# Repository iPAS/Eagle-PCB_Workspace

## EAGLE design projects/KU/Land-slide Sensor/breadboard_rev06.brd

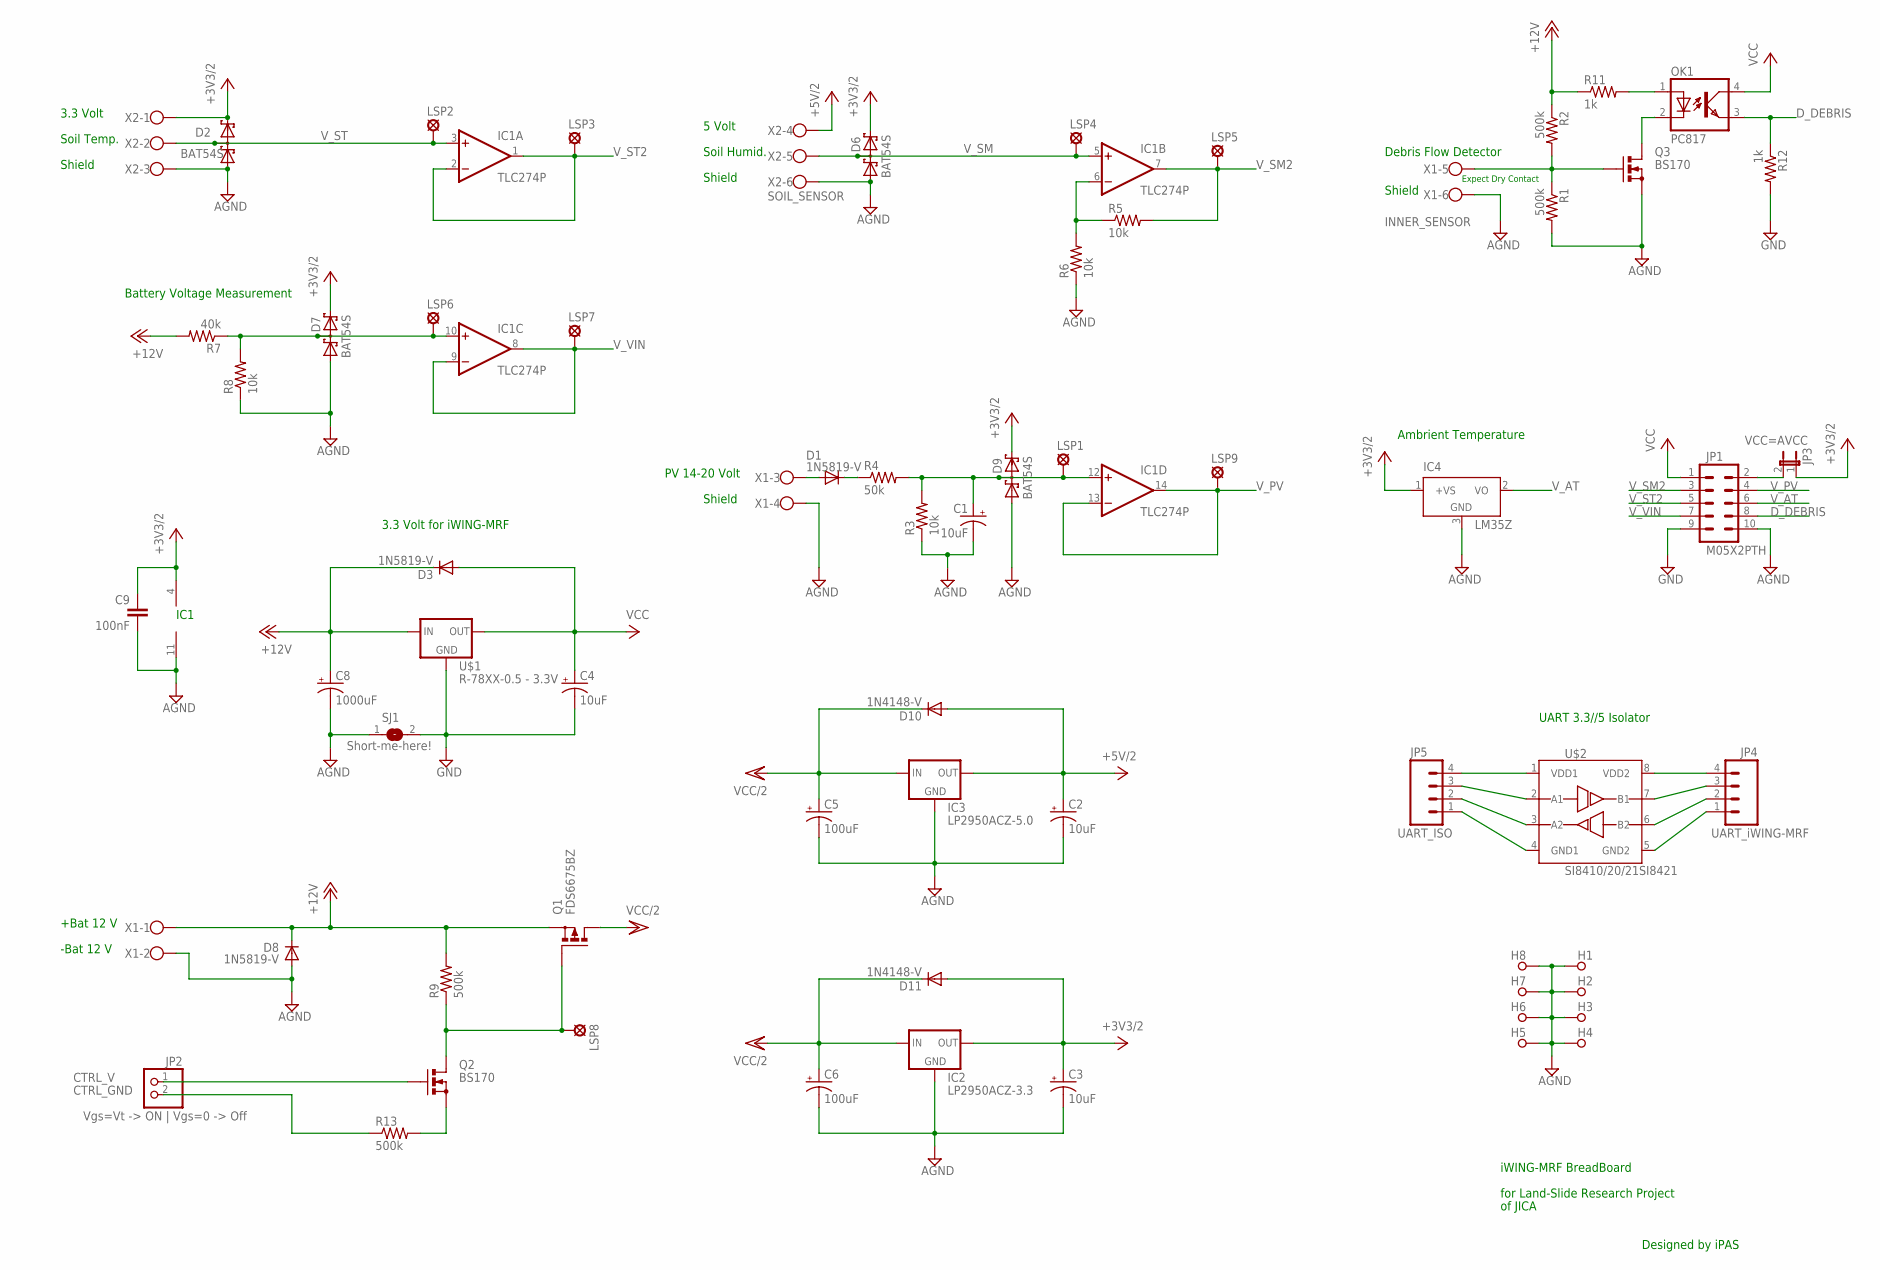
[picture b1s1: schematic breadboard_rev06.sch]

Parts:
C1, C2, C3, C4: 10uF; RCL_E2,5-7
C5, C6: 100uF; RCL_E2,5-7
C8: 1000uF; RCL_E5-13
C9: 100nF; RCL_C050-025X075
D1, D3, D8: 1N5819-V; DO41-150V
D2, D6, D7, D9: BAT54S; SOT23
D10, D11: 1N4148-V; DO35-100V
H1, H2, H3, H4, H5, H6, H7, H8: SPECIAL_DRILL_0.1560; PAD_0.1560
IC1: TLC274P; DIL14
IC2: LP2950ACZ-3.3; TO92
IC3: LP2950ACZ-5.0; TO92
IC4: LM35Z; TO92
JP1: M05X2PTH; AVR_ICSP
JP2: Vgs=Vt -> ON | Vgs=0 -> Off; 1X02
JP3: VCC=AVCC; JUMPER_JP1
JP4: UART_iWING-MRF; MOLEX-1X4
JP5: UART_ISO; MOLEX-1X4
LSP1, LSP2, LSP3, LSP4, LSP5, LSP6, LSP7, LSP8, LSP9: LSP13
OK1: PC817; DIL04
Q1: FDS6675BZ; SO-08
Q2, Q3: BS170; SOT54E
R1, R2, R9, R13: 500k; RCL_0204/7
R3, R5, R6, R8: 10k; RCL_0204/7
R4: 50k; RCL_0204/7
R7: 40k; RCL_0204/7
R11, R12: 1k; RCL_0204/7
SJ1: Short-me-here!; SJ
U$1: R-78XX-0.5 - 3.3V; SIP3
U$2: SI8410/20/21SI8421; SO-08
X1: INNER_SENSOR; 5EHDRC-6P
X2: SOIL_SENSOR; 5EHDRC-6P

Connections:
+3V3/2: C3.+, C9.1, D2.2 (C2), D6.2 (C2), D7.2 (C2), D9.2 (C2), D11.A, IC1.4 (V+), IC2.1 (OUT), IC4.1 (+VS), JP3.1, X2.1
+5V/2: C2.+, D10.A, IC3.1 (OUT), X2.4
+12V: C8.+, D3.C, D8.C, Q1.1 (S), Q1.2 (S), Q1.3 (S), R2.1, R7.2, R9.2, R11.1, U$1.1 (IN), X1.1
AGND: C1.-, C2.-, C3.-, C5.-, C6.-, C8.-, C9.2, D2.1 (A1), D6.1 (A1), D7.1 (A1), D8.A, D9.1 (A1), H1.1, H2.1, H3.1, H4.1, H5.1, H6.1, H7.1, H8.1, IC1.11 (V-), IC2.2 (GND), IC3.2 (GND), IC4.3 (GND), JP1.10, Q3.S, R1.2, R3.1, R6.1, R8.1, SJ1.1, X1.2, X1.4, X1.6, X2.3, X2.6
CTRL_GND: JP2.2, R13.1
CTRL_V: JP2.1, Q2.G
D_DEBRIS: JP1.8, OK1.3 (EMIT), R12.1
GND: C4.-, JP1.9, R12.2, SJ1.2, U$1.2 (GND)
unnamed: D7.3 (C1A2), IC1.10 (+IN), LSP6.MP, R7.1, R8.2
unnamed: IC1.6 (-IN), R5.1, R6.2
unnamed: LSP8.MP, Q1.4 (G), Q2.D, R9.1
unnamed: JP1.2, JP3.2
unnamed: OK1.1 (A), R11.2
unnamed: Q2.S, R13.2
unnamed: OK1.2 (C), Q3.D
unnamed: Q3.G, R1.1, R2.2, X1.5
unnamed: D1.A, X1.3
unnamed: JP4.4, U$2.8 (VDD2)
unnamed: D1.C, R4.1
unnamed: JP4.1, U$2.5 (GND2)
unnamed: JP5.4, U$2.1 (VDD1)
unnamed: JP5.3, U$2.2 (A1)
unnamed: C1.+, D9.3 (C1A2), IC1.12 (+IN), LSP1.MP, R3.2, R4.2
unnamed: JP5.2, U$2.3 (A2)
unnamed: JP5.1, U$2.4 (GND1)
RX: JP4.3, U$2.7 (B1)
TX: JP4.2, U$2.6 (B2)
VCC: C4.+, D3.A, JP1.1, OK1.4 (COL), U$1.3 (OUT)
VCC/2: C5.+, C6.+, D10.C, D11.C, IC2.3 (IN), IC3.3 (IN), Q1.5 (D), Q1.6 (D), Q1.7 (D), Q1.8 (D)
V_AT: IC4.2 (VO), JP1.6
V_PV: IC1.13 (-IN), IC1.14 (OUT), JP1.4, LSP9.MP
V_SM: D6.3 (C1A2), IC1.5 (+IN), LSP4.MP, X2.5
V_SM2: IC1.7 (OUT), JP1.3, LSP5.MP, R5.2
V_ST: D2.3 (C1A2), IC1.3 (+IN), LSP2.MP, X2.2
V_ST2: IC1.1 (OUT), IC1.2 (-IN), JP1.5, LSP3.MP
V_VIN: IC1.8 (OUT), IC1.9 (-IN), JP1.7, LSP7.MP

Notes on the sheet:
+Bat 12 V
PV 14-20 Volt
Debris Flow Detector
Ambrient Temperature
IC1
3.3 Volt for iWING-MRF
Battery Voltage Measurement
Expect Dry Contact
UART 3.3//5 Isolator
3.3 Volt
Soil Temp.
Shield
5 Volt
Soil Humid.
-Bat 12 V
iWING-MRF BreadBoard
for Land-Slide Research Project
of JICA
Designed by iPAS

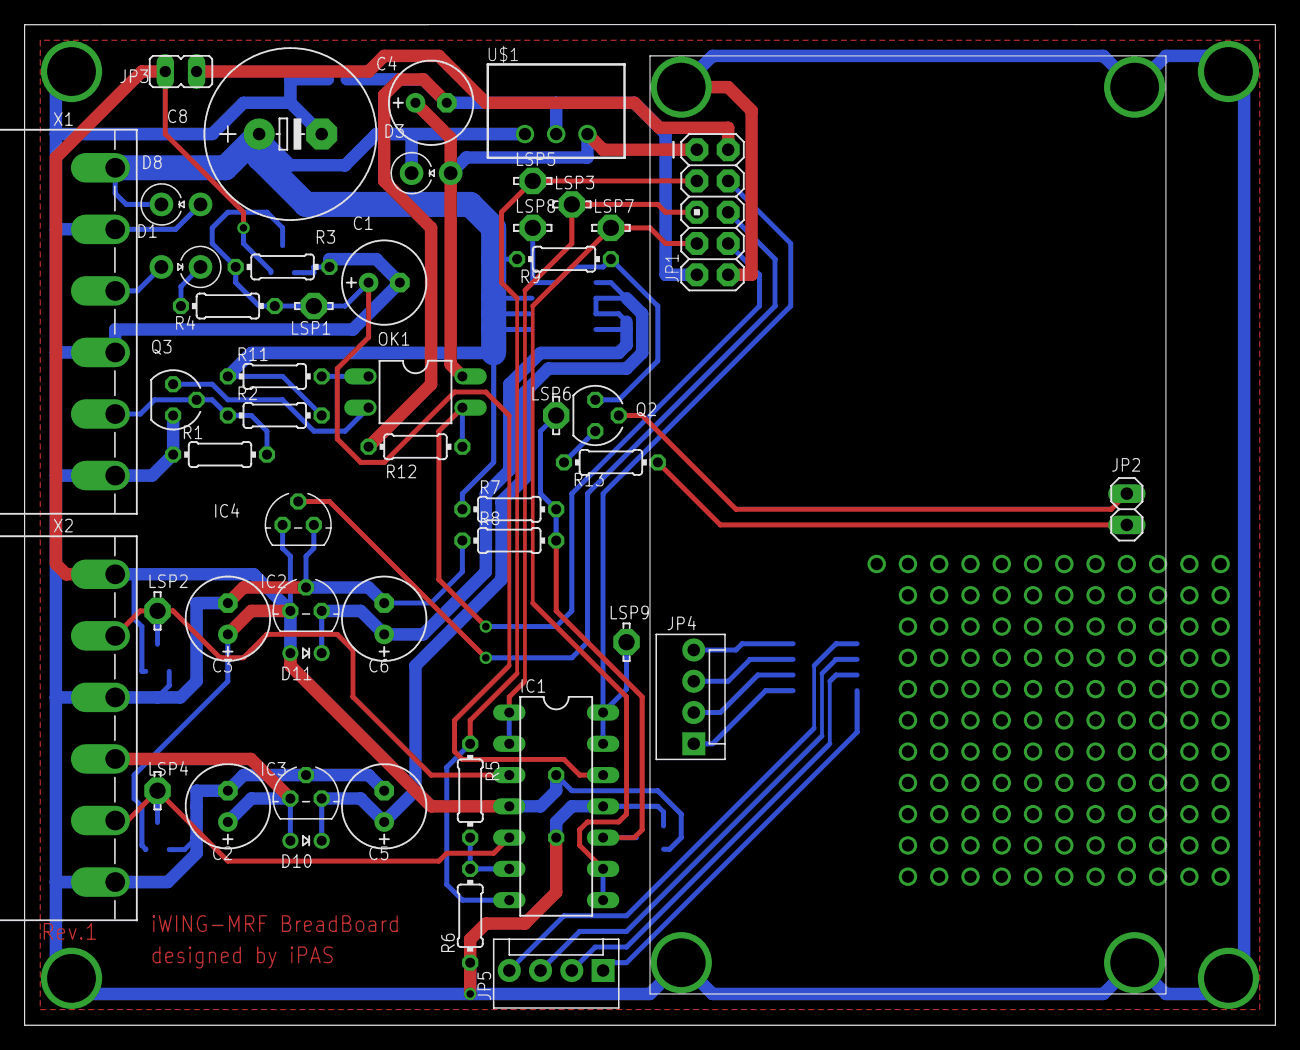
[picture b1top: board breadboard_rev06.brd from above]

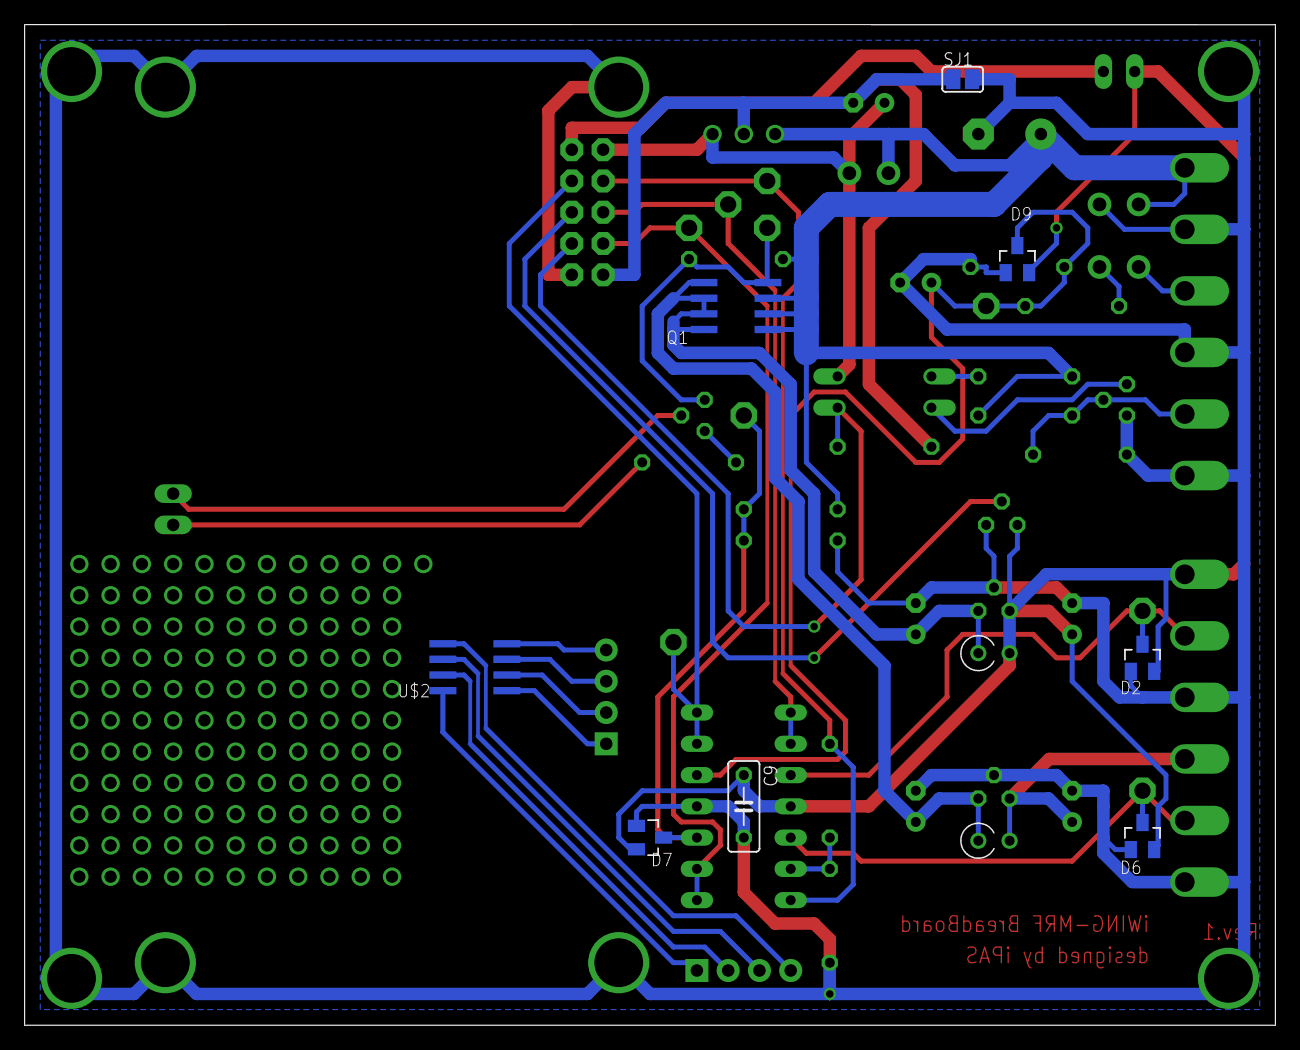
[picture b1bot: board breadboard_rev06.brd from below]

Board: 2 copper layers, 101.6 x 81.3 mm, 64 parts (8 on the bottom side), 36 nets.

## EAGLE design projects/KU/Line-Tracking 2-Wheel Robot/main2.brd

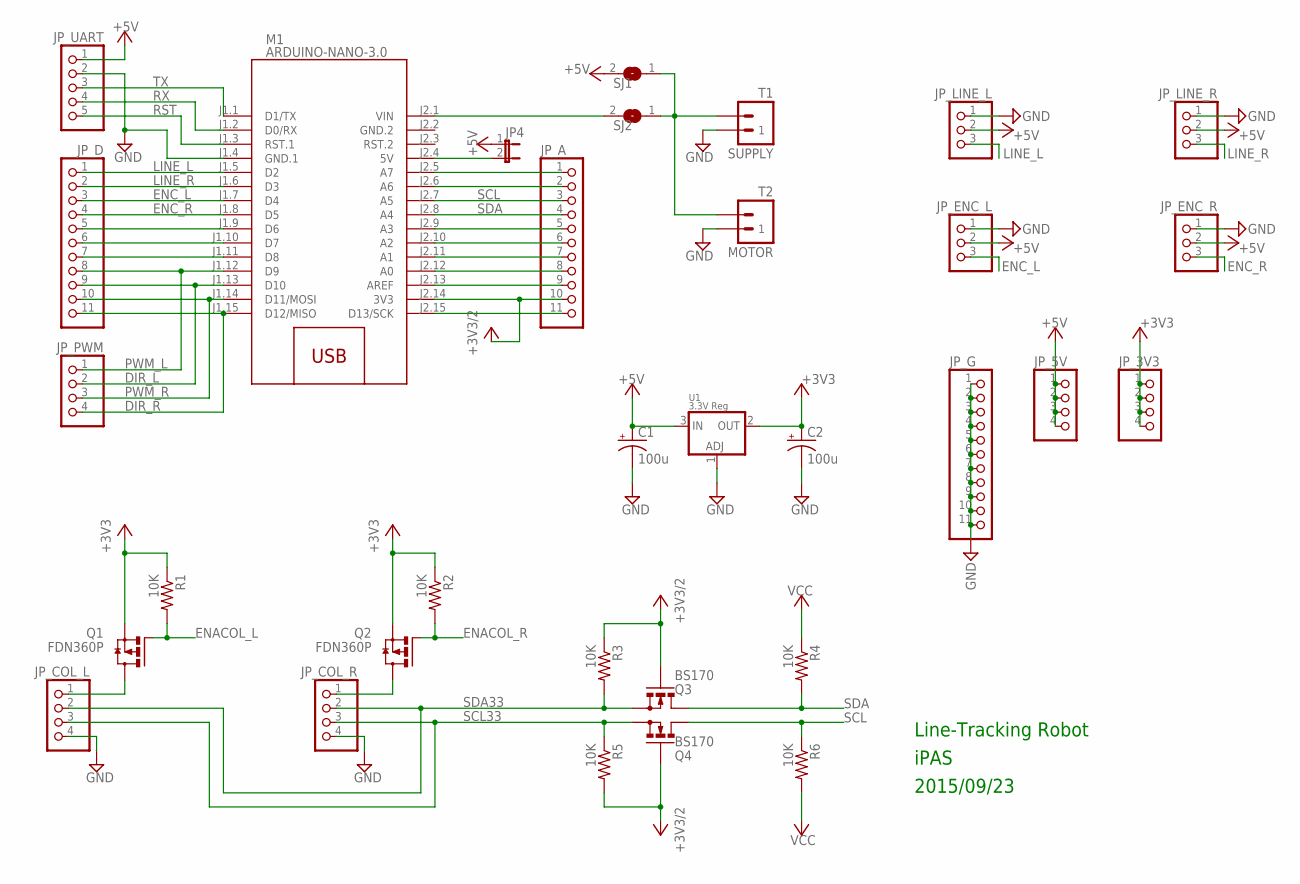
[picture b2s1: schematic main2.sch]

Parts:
C1, C2: 100u; RCL_E2,5-6
JP4: JUMPER2
JP_3V3, JP_5V: HEADER-1X4ROUND; 1X04_ROUND
JP_A: HEADER-1X11; 1X11_ROUND
JP_COL_L: HEADER-1X4ROUND; 1X04_ROUND
JP_COL_R: HEADER-1X4ROUND; 1X04_ROUND
JP_D: HEADER-1X11; 1X11_ROUND
JP_ENC_L: HEADER-1X3ROUND; 1X03_ROUND
JP_ENC_R: HEADER-1X3ROUND; 1X03_ROUND
JP_G: HEADER-1X11; 1X11_ROUND
JP_LINE_L: HEADER-1X3ROUND; 1X03_ROUND
JP_LINE_R: HEADER-1X3ROUND; 1X03_ROUND
JP_PWM: HEADER-1X4ROUND; 1X04_ROUND
JP_UART: HEADER-1X5ROUND; 1X05_ROUND
M1: ARDUINO-NANO-3.0
Q1, Q2: FDN360P; SUPER-SOT3
Q3, Q4: BS170; TO92-
R1, R2, R3, R4, R5, R6: 10K; RCL_0204/5
SJ1, SJ2: SOLDERJUMPERREFLOW; SOLDERJUMPER_REFLOW
T1: SUPPLY; DG381-02P
T2: MOTOR; DG381-02P
U1: 3.3V Reg; SOT223-R

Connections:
+3V3: C2.+, JP_3V3.1, JP_3V3.2, JP_3V3.3, JP_3V3.4, Q1.2 (S), Q2.2 (S), R1.1, R2.1, U1.2 (OUT)
+3V3/2: JP_A.10, M1.J2.14 (3V3), Q3.2 (G), Q4.2 (G), R3.1, R5.2
+5V: C1.+, JP4.1, JP_5V.1, JP_5V.2, JP_5V.3, JP_5V.4, JP_ENC_L.2, JP_ENC_R.2, JP_LINE_L.2, JP_LINE_R.2, JP_UART.1, SJ1.2, U1.3 (IN)
DIR_L: JP_D.9, JP_PWM.2, M1.J1.13 (D10)
DIR_R: JP_D.11, JP_PWM.4, M1.J1.15 (D12/MISO)
ENACOL_L: Q1.1 (G), R1.2
ENACOL_R: Q2.1 (G), R2.2
ENC_L: JP_D.3, JP_ENC_L.3, M1.J1.7 (D4)
ENC_R: JP_D.4, JP_ENC_R.3, M1.J1.8 (D5)
GND: C1.-, C2.-, JP_COL_L.4, JP_COL_R.4, JP_ENC_L.1, JP_ENC_R.1, JP_G.1, JP_G.2, JP_G.3, JP_G.4, JP_G.5, JP_G.6, JP_G.7, JP_G.8, JP_G.9, JP_G.10, JP_G.11, JP_LINE_L.1, JP_LINE_R.1, JP_UART.2, M1.J1.4 (GND.1), T1.1, T2.1, U1.1 (ADJ)
GND.2: M1.J2.2 (GND.2)
LINE_L: JP_D.1, JP_LINE_L.3, M1.J1.5 (D2)
LINE_R: JP_D.2, JP_LINE_R.3, M1.J1.6 (D3)
unnamed: JP_COL_R.1, Q2.3 (D)
unnamed: JP_A.1, M1.J2.5 (A7)
unnamed: JP_COL_L.1, Q1.3 (D)
unnamed: JP_A.2, M1.J2.6 (A6)
unnamed: JP4.2, M1.J2.4 (5V)
unnamed: M1.J2.1 (VIN), SJ2.2
unnamed: SJ1.1, SJ2.1, T1.2, T2.2
unnamed: JP_D.5, M1.J1.9 (D6)
unnamed: JP_D.6, M1.J1.10 (D7)
unnamed: JP_D.7, M1.J1.11 (D8)
unnamed: JP_A.5, M1.J2.9 (A3)
unnamed: JP_A.6, M1.J2.10 (A2)
unnamed: JP_A.7, M1.J2.11 (A1)
unnamed: JP_A.8, M1.J2.12 (A0)
unnamed: JP_A.9, M1.J2.13 (AREF)
unnamed: JP_A.11, M1.J2.15 (D13/SCK)
PWM_L: JP_D.8, JP_PWM.1, M1.J1.12 (D9)
PWM_R: JP_D.10, JP_PWM.3, M1.J1.14 (D11/MOSI)
RST: JP_UART.5, M1.J1.3 (RST.1)
RX: JP_UART.4, M1.J1.2 (D0/RX)
SCL: JP_A.3, M1.J2.7 (A5), Q4.1 (D), R6.1
SCL33: JP_COL_L.3, JP_COL_R.3, Q4.3 (S), R5.1
SDA: JP_A.4, M1.J2.8 (A4), Q3.1 (D), R4.2
SDA33: JP_COL_L.2, JP_COL_R.2, Q3.3 (S), R3.2
TX: JP_UART.3, M1.J1.1 (D1/TX)
VCC: R4.1, R6.2

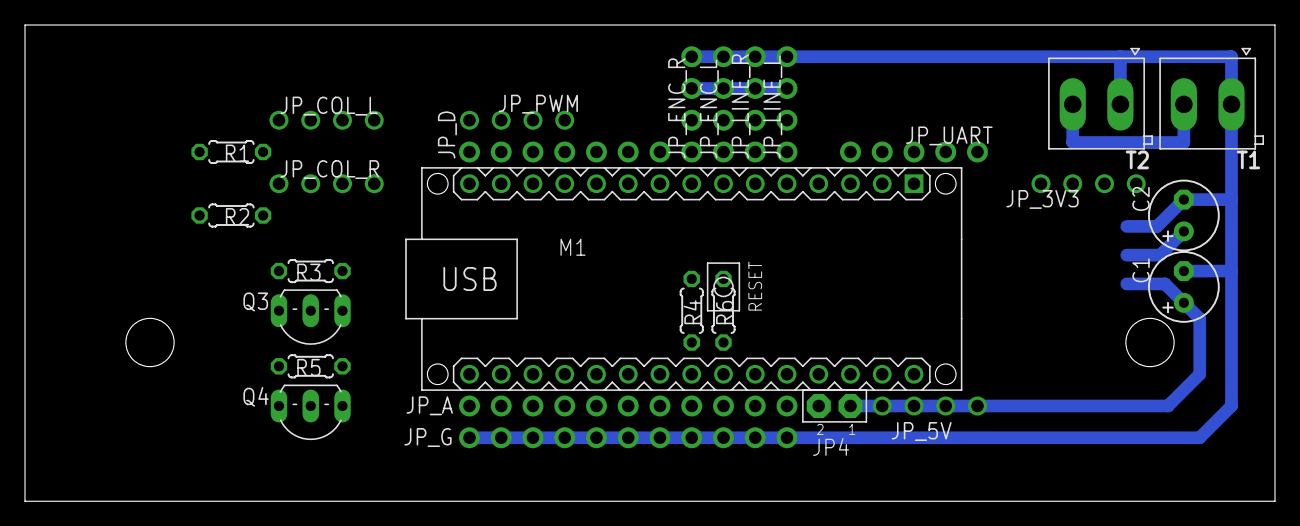
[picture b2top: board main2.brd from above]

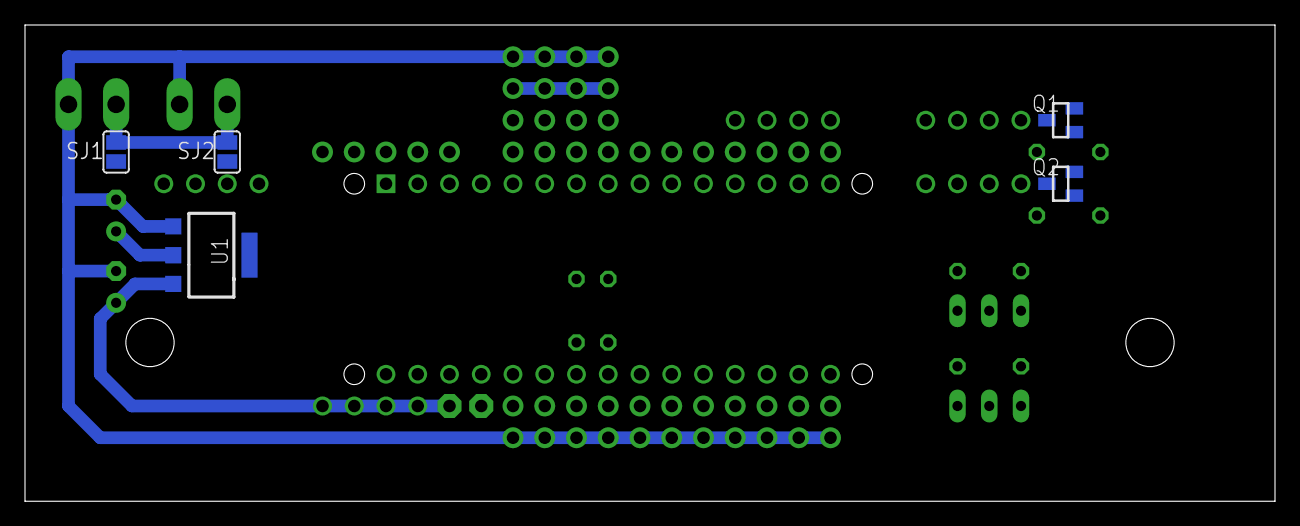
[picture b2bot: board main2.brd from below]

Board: 2 copper layers, 100.0 x 38.1 mm, 32 parts (5 on the bottom side), 38 nets.

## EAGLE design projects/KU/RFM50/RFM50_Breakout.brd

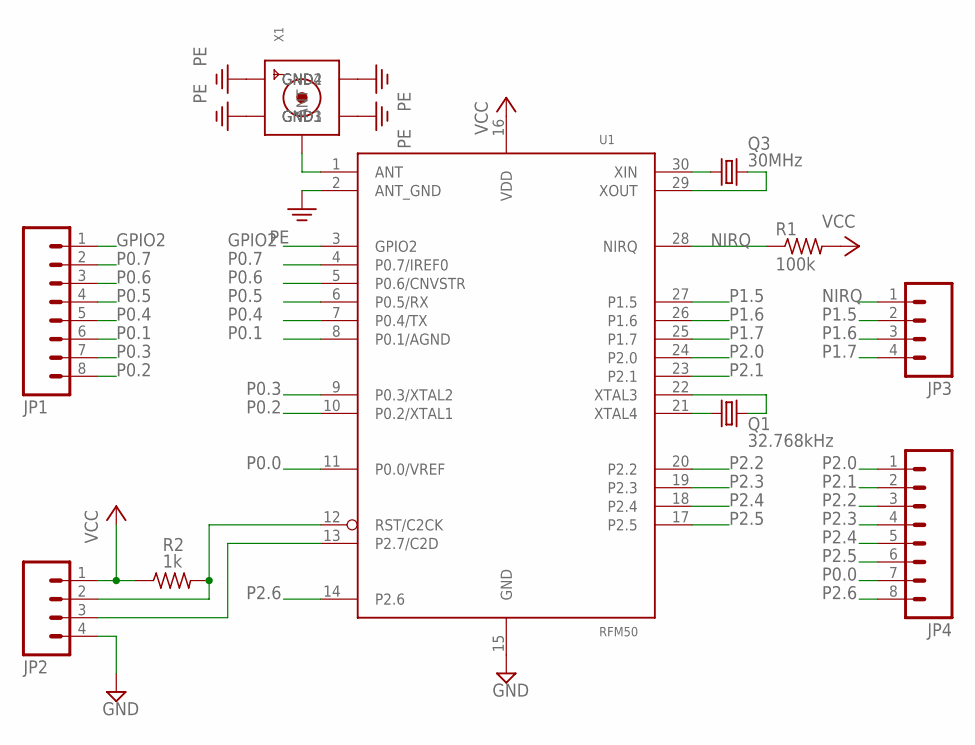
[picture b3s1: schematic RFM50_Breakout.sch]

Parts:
JP1, JP4: M081X08; 1X08
JP2, JP3: M04PTH; 1X04
Q1: 32.768kHz; TC26H
Q3: 30MHz; HC49/S
R1: 100k; RCL_0204V
R2: 1k; RCL_0204V
U1: RFM50
X1: SMACONNECTOR; SMA90_DIP

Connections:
GND: JP2.4, U1.15 (GND)
GPIO2: JP1.1, U1.3 (GPIO2)
unnamed: U1.1 (ANT), X1.ANTENNA (ANT)
unnamed: JP2.2, R2.2, U1.12 (RST/C2CK)
unnamed: Q3.1, U1.30 (XIN)
unnamed: Q3.2, U1.29 (XOUT)
unnamed: Q1.2, U1.21 (XTAL4)
unnamed: Q1.1, U1.22 (XTAL3)
unnamed: JP2.3, U1.13 (P2.7/C2D)
NIRQ: JP3.1, R1.1, U1.28 (NIRQ)
P0.0: JP4.7, U1.11 (P0.0/VREF)
P0.1: JP1.6, U1.8 (P0.1/AGND)
P0.2: JP1.8, U1.10 (P0.2/XTAL1)
P0.3: JP1.7, U1.9 (P0.3/XTAL2)
P0.4: JP1.5, U1.7 (P0.4/TX)
P0.5: JP1.4, U1.6 (P0.5/RX)
P0.6: JP1.3, U1.5 (P0.6/CNVSTR)
P0.7: JP1.2, U1.4 (P0.7/IREF0)
P1.5: JP3.2, U1.27 (P1.5)
P1.6: JP3.3, U1.26 (P1.6)
P1.7: JP3.4, U1.25 (P1.7)
P2.0: JP4.1, U1.24 (P2.0)
P2.1: JP4.2, U1.23 (P2.1)
P2.2: JP4.3, U1.20 (P2.2)
P2.3: JP4.4, U1.19 (P2.3)
P2.4: JP4.5, U1.18 (P2.4)
P2.5: JP4.6, U1.17 (P2.5)
P2.6: JP4.8, U1.14 (P2.6)
PE: U1.2 (ANT_GND), X1.GND1, X1.GND2, X1.GND3, X1.GND4
VCC: JP2.1, R1.2, R2.1, U1.16 (VDD)

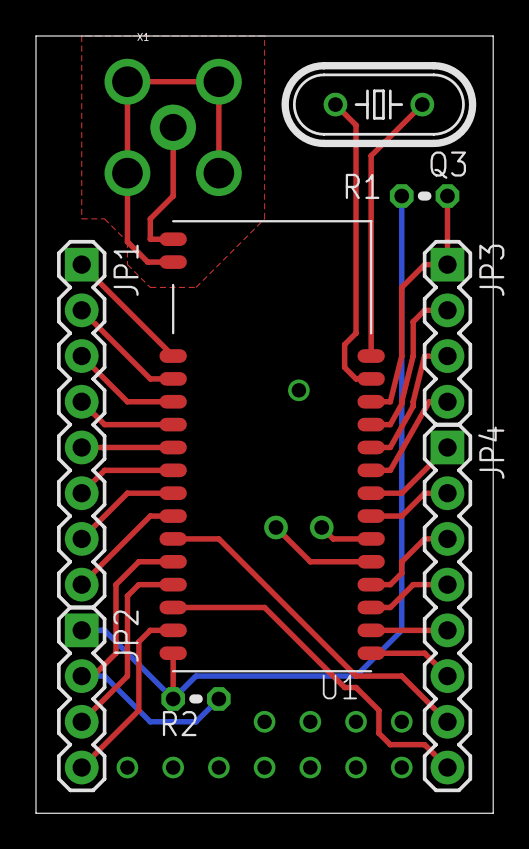
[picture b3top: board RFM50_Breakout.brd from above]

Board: 2 copper layers, 25.4 x 43.2 mm, 10 parts (1 on the bottom side), 30 nets.

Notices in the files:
parts and their libraries:
SparkFun-Connectors: Licensing: CC v3.0 Share-Alike You are welcome to use this library for commercial purposes.
diy-modules: Released under the Creative Commons Attribution 4.0 International License: http://creativecommons.org/licenses/by/4.0
